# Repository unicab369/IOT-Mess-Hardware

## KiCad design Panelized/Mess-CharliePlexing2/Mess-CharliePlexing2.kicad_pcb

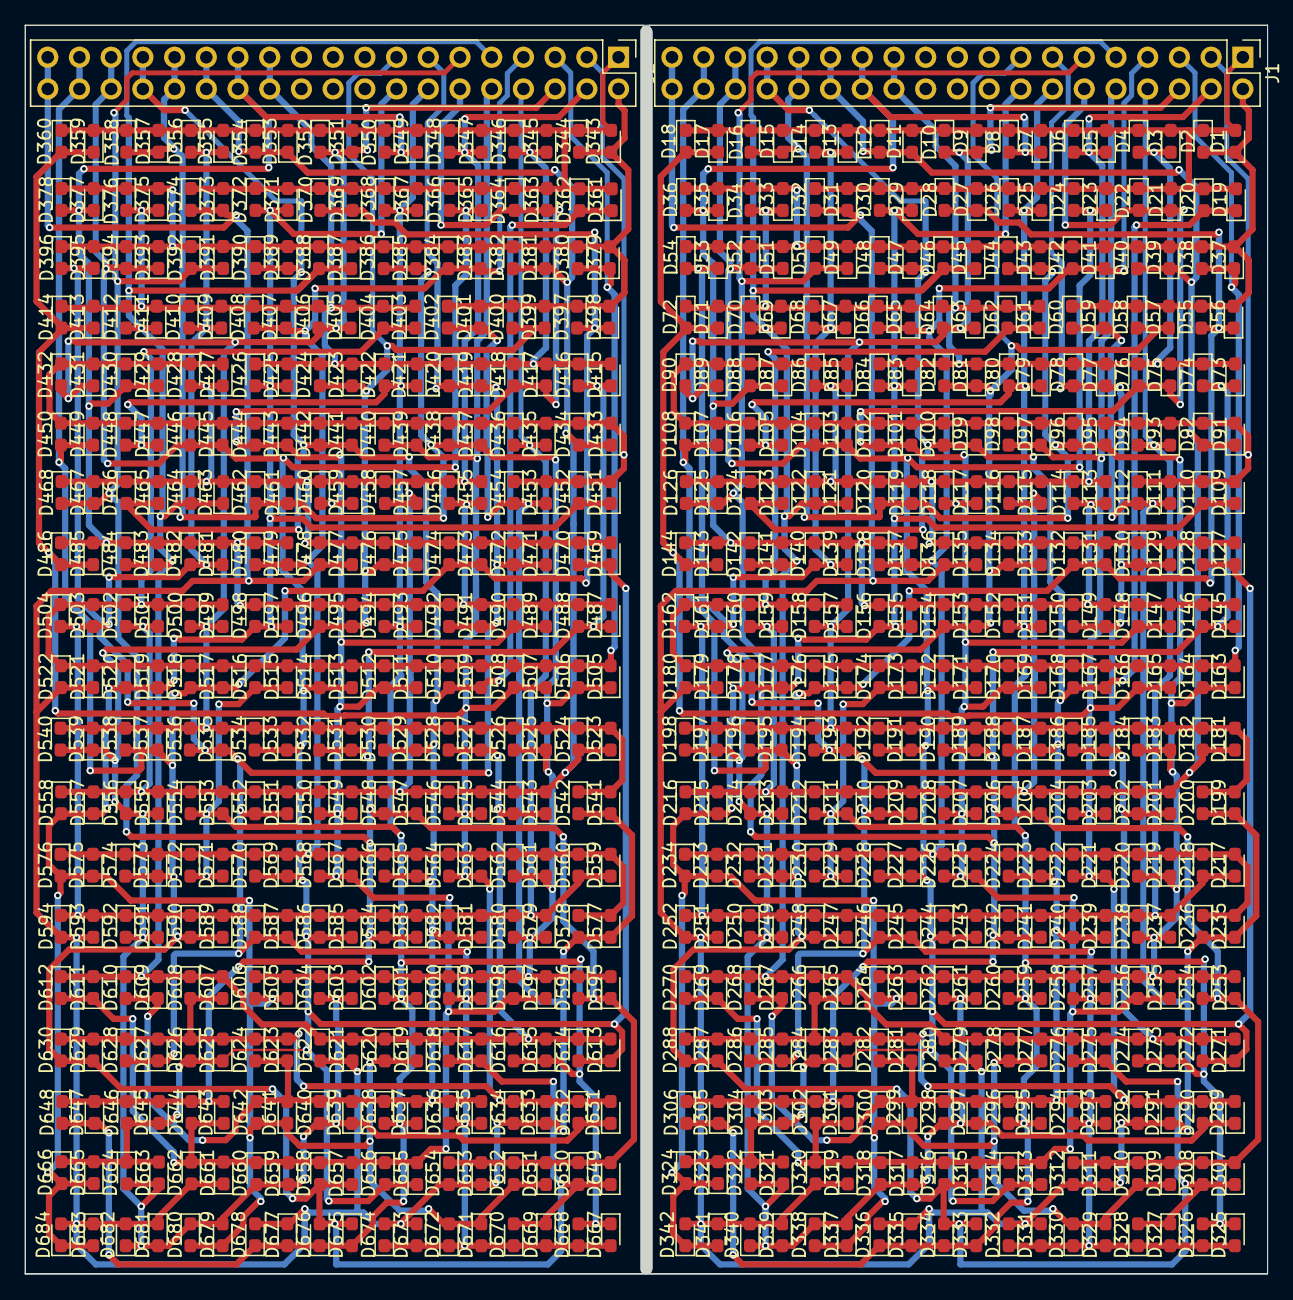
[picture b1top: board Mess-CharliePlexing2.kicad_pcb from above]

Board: 2 copper layers, 99.5 x 100.0 mm, 686 parts (0 on the bottom side), 24 nets.

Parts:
D1, D2, D3, D4, D5, D6, D7, D8, D9, D10, D11, D12, D13, D14, D15, D16, D17, D18, D19, D20, D21, D22, D23, D24, D25, D26, D27, D28, D29, D30, D31, D32, D33, D34, D35, D36, D37, D38, D39, D40, D41, D42, D43, D44, D45, D46, D47, D48, D49, D50, D51, D52, D53, D54, D55, D56, D57, D58, D59, D60, D61, D62, D63, D64, D65, D66, D67, D68, D69, D70, D71, D72, D73, D74, D75, D76, D77, D78, D79, D80, D81, D82, D83, D84, D85, D86, D87, D88, D89, D90, D91, D92, D93, D94, D95, D96, D97, D98, D99, D100, D101, D102, D103, D104, D105, D106, D107, D108, D109, D110, D111, D112, D113, D114, D115, D116, D117, D118, D119, D120, D121, D122, D123, D124, D125, D126, D127, D128, D129, D130, D131, D132, D133, D134, D135, D136, D137, D138, D139, D140, D141, D142, D143, D144, D145, D146, D147, D148, D149, D150, D151, D152, D153, D154, D155, D156, D157, D158, D159, D160, D161, D162, D163, D164, D165, D166, D167, D168, D169, D170, D171, D172, D173, D174, D175, D176, D177, D178, D179, D180, D181, D182, D183, D184, D185, D186, D187, D188, D189, D190, D191, D192, D193, D194, D195, D196, D197, D198, D199, D200, D201, D202, D203, D204, D205, D206, D207, D208, D209, D210, D211, D212, D213, D214, D215, D216, D217, D218, D219, D220, D221, D222, D223, D224, D225, D226, D227, D228, D229, D230, D231, D232, D233, D234, D235, D236, D237, D238, D239, D240, D241, D242, D243, D244, D245, D246, D247, D248, D249, D250, D251, D252, D253, D254, D255, D256, D257, D258, D259, D260, D261, D262, D263, D264, D265, D266, D267, D268, D269, D270, D271, D272, D273, D274, D275, D276, D277, D278, D279, D280, D281, D282, D283, D284, D285, D286, D287, D288, D289, D290, D291, D292, D293, D294, D295, D296, D297, D298, D299, D300, D301, D302, D303, D304, D305, D306, D307, D308, D309, D310, D311, D312, D313, D314, D315, D316, D317, D318, D319, D320, D321, D322, D323, D324, D325, D326, D327, D328, D329, D330, D331, D332, D333, D334, D335, D336, D337, D338, D339, D340, D341, D342, D343, D344, D345, D346, D347, D348, D349, D350, D351, D352, D353, D354, D355, D356, D357, D358, D359, D360, D361, D362, D363, D364, D365, D366, D367, D368, D369, D370, D371, D372, D373, D374, D375, D376, D377, D378, D379, D380, D381, D382, D383, D384, D385, D386, D387, D388, D389, D390, D391, D392, D393, D394, D395, D396, D397, D398, D399, D400, D401, D402, D403, D404, D405, D406, D407, D408, D409, D410, D411, D412, D413, D414, D415, D416, D417, D418, D419, D420, D421, D422, D423, D424, D425, D426, D427, D428, D429, D430, D431, D432, D433, D434, D435, D436, D437, D438, D439, D440, D441, D442, D443, D444, D445, D446, D447, D448, D449, D450, D451, D452, D453, D454, D455, D456, D457, D458, D459, D460, D461, D462, D463, D464, D465, D466, D467, D468, D469, D470, D471, D472, D473, D474, D475, D476, D477, D478, D479, D480, D481, D482, D483, D484, D485, D486, D487, D488, D489, D490, D491, D492, D493, D494, D495, D496, D497, D498, D499, D500, D501, D502, D503, D504, D505, D506, D507, D508, D509, D510, D511, D512, D513, D514, D515, D516, D517, D518, D519, D520, D521, D522, D523, D524, D525, D526, D527, D528, D529, D530, D531, D532, D533, D534, D535, D536, D537, D538, D539, D540, D541, D542, D543, D544, D545, D546, D547, D548, D549, D550, D551, D552, D553, D554, D555, D556, D557, D558, D559, D560, D561, D562, D563, D564, D565, D566, D567, D568, D569, D570, D571, D572, D573, D574, D575, D576, D577, D578, D579, D580, D581, D582, D583, D584, D585, D586, D587, D588, D589, D590, D591, D592, D593, D594, D595, D596, D597, D598, D599, D600, D601, D602, D603, D604, D605, D606, D607, D608, D609, D610, D611, D612, D613, D614, D615, D616, D617, D618, D619, D620, D621, D622, D623, D624, D625, D626, D627, D628, D629, D630, D631, D632, D633, D634, D635, D636, D637, D638, D639, D640, D641, D642, D643, D644, D645, D646, D647, D648, D649, D650, D651, D652, D653, D654, D655, D656, D657, D658, D659, D660, D661, D662, D663, D664, D665, D666, D667, D668, D669, D670, D671, D672, D673, D674, D675, D676, D677, D678, D679, D680, D681, D682, D683, D684: LED; LED_0603_1608Metric_Pad1.05x0.95mm_HandSolder
J1, J2: Conn_02x19_Odd_Even; PinHeader_2x19_P2.54mm_Vertical

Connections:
A_0: D1.2 (A), D2.1 (K), D3.2 (A), D4.1 (K), D5.2 (A), D6.1 (K), D7.2 (A), D8.1 (K), D9.2 (A), D10.1 (K), D11.2 (A), D12.1 (K), D13.2 (A), D14.1 (K), D15.2 (A), D16.1 (K), D17.2 (A), D18.1 (K), D19.2 (A), D20.1 (K), D21.2 (A), D22.1 (K), D23.2 (A), D24.1 (K), D25.2 (A), D26.1 (K), D27.2 (A), D28.1 (K), D29.2 (A), D30.1 (K), D31.2 (A), D32.1 (K), D343.2 (A), D344.1 (K), D345.2 (A), D346.1 (K), D347.2 (A), D348.1 (K), D349.2 (A), D350.1 (K), D351.2 (A), D352.1 (K), D353.2 (A), D354.1 (K), D355.2 (A), D356.1 (K), D357.2 (A), D358.1 (K), D359.2 (A), D360.1 (K), D361.2 (A), D362.1 (K), D363.2 (A), D364.1 (K), D365.2 (A), D366.1 (K), D367.2 (A), D368.1 (K), D369.2 (A), D370.1 (K), D371.2 (A), D372.1 (K), D373.2 (A), D374.1 (K), J1.1, J2.1
A_1: D85.2 (A), D86.1 (K), D87.2 (A), D88.1 (K), D89.2 (A), D90.1 (K), D91.2 (A), D92.1 (K), D93.2 (A), D94.1 (K), D95.2 (A), D96.1 (K), D97.2 (A), D98.1 (K), D99.2 (A), D100.1 (K), D101.2 (A), D102.1 (K), D103.2 (A), D104.1 (K), D105.2 (A), D106.1 (K), D107.2 (A), D108.1 (K), D109.2 (A), D110.1 (K), D111.2 (A), D112.1 (K), D427.2 (A), D428.1 (K), D429.2 (A), D430.1 (K), D431.2 (A), D432.1 (K), D433.2 (A), D434.1 (K), D435.2 (A), D436.1 (K), D437.2 (A), D438.1 (K), D439.2 (A), D440.1 (K), D441.2 (A), D442.1 (K), D443.2 (A), D444.1 (K), D445.2 (A), D446.1 (K), D447.2 (A), D448.1 (K), D449.2 (A), D450.1 (K), D451.2 (A), D452.1 (K), D453.2 (A), D454.1 (K), J1.3, J2.3
A_2: D37.1 (K), D38.2 (A), D61.1 (K), D62.2 (A), D157.2 (A), D158.1 (K), D159.2 (A), D160.1 (K), D161.2 (A), D162.1 (K), D163.2 (A), D164.1 (K), D165.2 (A), D166.1 (K), D167.2 (A), D168.1 (K), D169.2 (A), D170.1 (K), D171.2 (A), D172.1 (K), D173.2 (A), D174.1 (K), D175.2 (A), D176.1 (K), D177.2 (A), D178.1 (K), D179.2 (A), D180.1 (K), D379.1 (K), D380.2 (A), D403.1 (K), D404.2 (A), D499.2 (A), D500.1 (K), D501.2 (A), D502.1 (K), D503.2 (A), D504.1 (K), D505.2 (A), D506.1 (K), D507.2 (A), D508.1 (K), D509.2 (A), D510.1 (K), D511.2 (A), D512.1 (K), D513.2 (A), D514.1 (K), D515.2 (A), D516.1 (K), D517.2 (A), D518.1 (K), D519.2 (A), D520.1 (K), D521.2 (A), D522.1 (K), J1.5, J2.5
A_3: D41.1 (K), D42.2 (A), D65.1 (K), D66.2 (A), D117.1 (K), D118.2 (A), D137.1 (K), D138.2 (A), D217.2 (A), D218.1 (K), D219.2 (A), D220.1 (K), D221.2 (A), D222.1 (K), D223.2 (A), D224.1 (K), D225.2 (A), D226.1 (K), D227.2 (A), D228.1 (K), D229.2 (A), D230.1 (K), D231.2 (A), D232.1 (K), D233.2 (A), D234.1 (K), D235.2 (A), D236.1 (K), D383.1 (K), D384.2 (A), D407.1 (K), D408.2 (A), D459.1 (K), D460.2 (A), D479.1 (K), D480.2 (A), D559.2 (A), D560.1 (K), D561.2 (A), D562.1 (K), D563.2 (A), D564.1 (K), D565.2 (A), D566.1 (K), D567.2 (A), D568.1 (K), D569.2 (A), D570.1 (K), D571.2 (A), D572.1 (K), D573.2 (A), D574.1 (K), D575.2 (A), D576.1 (K), D577.2 (A), D578.1 (K), J1.7, J2.7
A_4: D45.1 (K), D46.2 (A), D69.1 (K), D70.2 (A), D121.1 (K), D122.2 (A), D141.1 (K), D142.2 (A), D185.1 (K), D186.2 (A), D201.1 (K), D202.2 (A), D265.2 (A), D266.1 (K), D267.2 (A), D268.1 (K), D269.2 (A), D270.1 (K), D271.2 (A), D272.1 (K), D273.2 (A), D274.1 (K), D275.2 (A), D276.1 (K), D277.2 (A), D278.1 (K), D279.2 (A), D280.1 (K), D387.1 (K), D388.2 (A), D411.1 (K), D412.2 (A), D463.1 (K), D464.2 (A), D483.1 (K), D484.2 (A), D527.1 (K), D528.2 (A), D543.1 (K), D544.2 (A), D607.2 (A), D608.1 (K), D609.2 (A), D610.1 (K), D611.2 (A), D612.1 (K), D613.2 (A), D614.1 (K), D615.2 (A), D616.1 (K), D617.2 (A), D618.1 (K), D619.2 (A), D620.1 (K), D621.2 (A), D622.1 (K), J1.9, J2.9
A_5: D49.1 (K), D50.2 (A), D73.1 (K), D74.2 (A), D125.1 (K), D126.2 (A), D145.1 (K), D146.2 (A), D189.1 (K), D190.2 (A), D205.1 (K), D206.2 (A), D241.1 (K), D242.2 (A), D253.1 (K), D254.2 (A), D301.2 (A), D302.1 (K), D303.2 (A), D304.1 (K), D305.2 (A), D306.1 (K), D307.2 (A), D308.1 (K), D309.2 (A), D310.1 (K), D311.2 (A), D312.1 (K), D391.1 (K), D392.2 (A), D415.1 (K), D416.2 (A), D467.1 (K), D468.2 (A), D487.1 (K), D488.2 (A), D531.1 (K), D532.2 (A), D547.1 (K), D548.2 (A), D583.1 (K), D584.2 (A), D595.1 (K), D596.2 (A), D643.2 (A), D644.1 (K), D645.2 (A), D646.1 (K), D647.2 (A), D648.1 (K), D649.2 (A), D650.1 (K), D651.2 (A), D652.1 (K), D653.2 (A), D654.1 (K), J1.11, J2.11
A_6: D53.1 (K), D54.2 (A), D77.1 (K), D78.2 (A), D129.1 (K), D130.2 (A), D149.1 (K), D150.2 (A), D193.1 (K), D194.2 (A), D209.1 (K), D210.2 (A), D245.1 (K), D246.2 (A), D257.1 (K), D258.2 (A), D285.1 (K), D286.2 (A), D293.1 (K), D294.2 (A), D325.2 (A), D326.1 (K), D327.2 (A), D328.1 (K), D329.2 (A), D330.1 (K), D331.2 (A), D332.1 (K), D395.1 (K), D396.2 (A), D419.1 (K), D420.2 (A), D471.1 (K), D472.2 (A), D491.1 (K), D492.2 (A), D535.1 (K), D536.2 (A), D551.1 (K), D552.2 (A), D587.1 (K), D588.2 (A), D599.1 (K), D600.2 (A), D627.1 (K), D628.2 (A), D635.1 (K), D636.2 (A), D667.2 (A), D668.1 (K), D669.2 (A), D670.1 (K), D671.2 (A), D672.1 (K), D673.2 (A), D674.1 (K), J1.13, J2.13
A_7: D57.1 (K), D58.2 (A), D81.1 (K), D82.2 (A), D133.1 (K), D134.2 (A), D153.1 (K), D154.2 (A), D197.1 (K), D198.2 (A), D213.1 (K), D214.2 (A), D249.1 (K), D250.2 (A), D261.1 (K), D262.2 (A), D289.1 (K), D290.2 (A), D297.1 (K), D298.2 (A), D317.1 (K), D318.2 (A), D321.1 (K), D322.2 (A), D337.2 (A), D338.1 (K), D339.2 (A), D340.1 (K), D399.1 (K), D400.2 (A), D423.1 (K), D424.2 (A), D475.1 (K), D476.2 (A), D495.1 (K), D496.2 (A), D539.1 (K), D540.2 (A), D555.1 (K), D556.2 (A), D591.1 (K), D592.2 (A), D603.1 (K), D604.2 (A), D631.1 (K), D632.2 (A), D639.1 (K), D640.2 (A), D659.1 (K), D660.2 (A), D663.1 (K), D664.2 (A), D679.2 (A), D680.1 (K), D681.2 (A), D682.1 (K), J1.15, J2.15
C_0: D3.1 (K), D4.2 (A), D33.1 (K), D34.2 (A), D61.2 (A), D62.1 (K), D63.2 (A), D64.1 (K), D65.2 (A), D66.1 (K), D67.2 (A), D68.1 (K), D69.2 (A), D70.1 (K), D71.2 (A), D72.1 (K), D73.2 (A), D74.1 (K), D75.2 (A), D76.1 (K), D77.2 (A), D78.1 (K), D79.2 (A), D80.1 (K), D81.2 (A), D82.1 (K), D83.2 (A), D84.1 (K), D345.1 (K), D346.2 (A), D375.1 (K), D376.2 (A), D403.2 (A), D404.1 (K), D405.2 (A), D406.1 (K), D407.2 (A), D408.1 (K), D409.2 (A), D410.1 (K), D411.2 (A), D412.1 (K), D413.2 (A), D414.1 (K), D415.2 (A), D416.1 (K), D417.2 (A), D418.1 (K), D419.2 (A), D420.1 (K), D421.2 (A), D422.1 (K), D423.2 (A), D424.1 (K), D425.2 (A), D426.1 (K), J1.23, J1.24, J2.23, J2.24
C_1: D7.1 (K), D8.2 (A), D35.1 (K), D36.2 (A), D87.1 (K), D88.2 (A), D113.1 (K), D114.2 (A), D137.2 (A), D138.1 (K), D139.2 (A), D140.1 (K), D141.2 (A), D142.1 (K), D143.2 (A), D144.1 (K), D145.2 (A), D146.1 (K), D147.2 (A), D148.1 (K), D149.2 (A), D150.1 (K), D151.2 (A), D152.1 (K), D153.2 (A), D154.1 (K), D155.2 (A), D156.1 (K), D349.1 (K), D350.2 (A), D377.1 (K), D378.2 (A), D429.1 (K), D430.2 (A), D455.1 (K), D456.2 (A), D479.2 (A), D480.1 (K), D481.2 (A), D482.1 (K), D483.2 (A), D484.1 (K), D485.2 (A), D486.1 (K), D487.2 (A), D488.1 (K), D489.2 (A), D490.1 (K), D491.2 (A), D492.1 (K), D493.2 (A), D494.1 (K), D495.2 (A), D496.1 (K), D497.2 (A), D498.1 (K), J1.25, J1.26, J2.25, J2.26
C_2: D11.1 (K), D12.2 (A), D39.1 (K), D40.2 (A), D91.1 (K), D92.2 (A), D115.1 (K), D116.2 (A), D159.1 (K), D160.2 (A), D181.1 (K), D182.2 (A), D201.2 (A), D202.1 (K), D203.2 (A), D204.1 (K), D205.2 (A), D206.1 (K), D207.2 (A), D208.1 (K), D209.2 (A), D210.1 (K), D211.2 (A), D212.1 (K), D213.2 (A), D214.1 (K), D215.2 (A), D216.1 (K), D353.1 (K), D354.2 (A), D381.1 (K), D382.2 (A), D433.1 (K), D434.2 (A), D457.1 (K), D458.2 (A), D501.1 (K), D502.2 (A), D523.1 (K), D524.2 (A), D543.2 (A), D544.1 (K), D545.2 (A), D546.1 (K), D547.2 (A), D548.1 (K), D549.2 (A), D550.1 (K), D551.2 (A), D552.1 (K), D553.2 (A), D554.1 (K), D555.2 (A), D556.1 (K), D557.2 (A), D558.1 (K), J1.27, J1.28, J2.27, J2.28
C_3: D15.1 (K), D16.2 (A), D43.1 (K), D44.2 (A), D95.1 (K), D96.2 (A), D119.1 (K), D120.2 (A), D163.1 (K), D164.2 (A), D183.1 (K), D184.2 (A), D219.1 (K), D220.2 (A), D237.1 (K), D238.2 (A), D253.2 (A), D254.1 (K), D255.2 (A), D256.1 (K), D257.2 (A), D258.1 (K), D259.2 (A), D260.1 (K), D261.2 (A), D262.1 (K), D263.2 (A), D264.1 (K), D357.1 (K), D358.2 (A), D385.1 (K), D386.2 (A), D437.1 (K), D438.2 (A), D461.1 (K), D462.2 (A), D505.1 (K), D506.2 (A), D525.1 (K), D526.2 (A), D561.1 (K), D562.2 (A), D579.1 (K), D580.2 (A), D595.2 (A), D596.1 (K), D597.2 (A), D598.1 (K), D599.2 (A), D600.1 (K), D601.2 (A), D602.1 (K), D603.2 (A), D604.1 (K), D605.2 (A), D606.1 (K), J1.29, J1.30, J2.29, J2.30
C_4: D19.1 (K), D20.2 (A), D47.1 (K), D48.2 (A), D99.1 (K), D100.2 (A), D123.1 (K), D124.2 (A), D167.1 (K), D168.2 (A), D187.1 (K), D188.2 (A), D223.1 (K), D224.2 (A), D239.1 (K), D240.2 (A), D267.1 (K), D268.2 (A), D281.1 (K), D282.2 (A), D293.2 (A), D294.1 (K), D295.2 (A), D296.1 (K), D297.2 (A), D298.1 (K), D299.2 (A), D300.1 (K), D361.1 (K), D362.2 (A), D389.1 (K), D390.2 (A), D441.1 (K), D442.2 (A), D465.1 (K), D466.2 (A), D509.1 (K), D510.2 (A), D529.1 (K), D530.2 (A), D565.1 (K), D566.2 (A), D581.1 (K), D582.2 (A), D609.1 (K), D610.2 (A), D623.1 (K), D624.2 (A), D635.2 (A), D636.1 (K), D637.2 (A), D638.1 (K), D639.2 (A), D640.1 (K), D641.2 (A), D642.1 (K), J1.31, J1.32, J2.31, J2.32
C_5: D23.1 (K), D24.2 (A), D51.1 (K), D52.2 (A), D103.1 (K), D104.2 (A), D127.1 (K), D128.2 (A), D171.1 (K), D172.2 (A), D191.1 (K), D192.2 (A), D227.1 (K), D228.2 (A), D243.1 (K), D244.2 (A), D271.1 (K), D272.2 (A), D283.1 (K), D284.2 (A), D303.1 (K), D304.2 (A), D313.1 (K), D314.2 (A), D321.2 (A), D322.1 (K), D323.2 (A), D324.1 (K), D365.1 (K), D366.2 (A), D393.1 (K), D394.2 (A), D445.1 (K), D446.2 (A), D469.1 (K), D470.2 (A), D513.1 (K), D514.2 (A), D533.1 (K), D534.2 (A), D569.1 (K), D570.2 (A), D585.1 (K), D586.2 (A), D613.1 (K), D614.2 (A), D625.1 (K), D626.2 (A), D645.1 (K), D646.2 (A), D655.1 (K), D656.2 (A), D663.2 (A), D664.1 (K), D665.2 (A), D666.1 (K), J1.33, J1.34, J2.33, J2.34
C_6: D27.1 (K), D28.2 (A), D55.1 (K), D56.2 (A), D107.1 (K), D108.2 (A), D131.1 (K), D132.2 (A), D175.1 (K), D176.2 (A), D195.1 (K), D196.2 (A), D231.1 (K), D232.2 (A), D247.1 (K), D248.2 (A), D275.1 (K), D276.2 (A), D287.1 (K), D288.2 (A), D307.1 (K), D308.2 (A), D315.1 (K), D316.2 (A), D327.1 (K), D328.2 (A), D333.1 (K), D334.2 (A), D369.1 (K), D370.2 (A), D397.1 (K), D398.2 (A), D449.1 (K), D450.2 (A), D473.1 (K), D474.2 (A), D517.1 (K), D518.2 (A), D537.1 (K), D538.2 (A), D573.1 (K), D574.2 (A), D589.1 (K), D590.2 (A), D617.1 (K), D618.2 (A), D629.1 (K), D630.2 (A), D649.1 (K), D650.2 (A), D657.1 (K), D658.2 (A), D669.1 (K), D670.2 (A), D675.1 (K), D676.2 (A), J1.35, J1.36, J2.35, J2.36
C_7: D31.1 (K), D32.2 (A), D59.1 (K), D60.2 (A), D111.1 (K), D112.2 (A), D135.1 (K), D136.2 (A), D179.1 (K), D180.2 (A), D199.1 (K), D200.2 (A), D235.1 (K), D236.2 (A), D251.1 (K), D252.2 (A), D279.1 (K), D280.2 (A), D291.1 (K), D292.2 (A), D311.1 (K), D312.2 (A), D319.1 (K), D320.2 (A), D331.1 (K), D332.2 (A), D335.1 (K), D336.2 (A), D339.1 (K), D340.2 (A), D341.1 (K), D342.2 (A), D373.1 (K), D374.2 (A), D401.1 (K), D402.2 (A), D453.1 (K), D454.2 (A), D477.1 (K), D478.2 (A), D521.1 (K), D522.2 (A), D541.1 (K), D542.2 (A), D577.1 (K), D578.2 (A), D593.1 (K), D594.2 (A), D621.1 (K), D622.2 (A), D633.1 (K), D634.2 (A), D653.1 (K), D654.2 (A), D661.1 (K), D662.2 (A), D673.1 (K), D674.2 (A), D677.1 (K), D678.2 (A), D681.1 (K), D682.2 (A), D683.1 (K), D684.2 (A), J1.37, J1.38, J2.37, J2.38
R_0: D1.1 (K), D2.2 (A), D33.2 (A), D34.1 (K), D35.2 (A), D36.1 (K), D37.2 (A), D38.1 (K), D39.2 (A), D40.1 (K), D41.2 (A), D42.1 (K), D43.2 (A), D44.1 (K), D45.2 (A), D46.1 (K), D47.2 (A), D48.1 (K), D49.2 (A), D50.1 (K), D51.2 (A), D52.1 (K), D53.2 (A), D54.1 (K), D55.2 (A), D56.1 (K), D57.2 (A), D58.1 (K), D59.2 (A), D60.1 (K), D343.1 (K), D344.2 (A), D375.2 (A), D376.1 (K), D377.2 (A), D378.1 (K), D379.2 (A), D380.1 (K), D381.2 (A), D382.1 (K), D383.2 (A), D384.1 (K), D385.2 (A), D386.1 (K), D387.2 (A), D388.1 (K), D389.2 (A), D390.1 (K), D391.2 (A), D392.1 (K), D393.2 (A), D394.1 (K), D395.2 (A), D396.1 (K), D397.2 (A), D398.1 (K), D399.2 (A), D400.1 (K), D401.2 (A), D402.1 (K), J1.2, J2.2
R_1: D5.1 (K), D6.2 (A), D85.1 (K), D86.2 (A), D113.2 (A), D114.1 (K), D115.2 (A), D116.1 (K), D117.2 (A), D118.1 (K), D119.2 (A), D120.1 (K), D121.2 (A), D122.1 (K), D123.2 (A), D124.1 (K), D125.2 (A), D126.1 (K), D127.2 (A), D128.1 (K), D129.2 (A), D130.1 (K), D131.2 (A), D132.1 (K), D133.2 (A), D134.1 (K), D135.2 (A), D136.1 (K), D347.1 (K), D348.2 (A), D427.1 (K), D428.2 (A), D455.2 (A), D456.1 (K), D457.2 (A), D458.1 (K), D459.2 (A), D460.1 (K), D461.2 (A), D462.1 (K), D463.2 (A), D464.1 (K), D465.2 (A), D466.1 (K), D467.2 (A), D468.1 (K), D469.2 (A), D470.1 (K), D471.2 (A), D472.1 (K), D473.2 (A), D474.1 (K), D475.2 (A), D476.1 (K), D477.2 (A), D478.1 (K), J1.4, J2.4
R_2: D9.1 (K), D10.2 (A), D63.1 (K), D64.2 (A), D89.1 (K), D90.2 (A), D157.1 (K), D158.2 (A), D181.2 (A), D182.1 (K), D183.2 (A), D184.1 (K), D185.2 (A), D186.1 (K), D187.2 (A), D188.1 (K), D189.2 (A), D190.1 (K), D191.2 (A), D192.1 (K), D193.2 (A), D194.1 (K), D195.2 (A), D196.1 (K), D197.2 (A), D198.1 (K), D199.2 (A), D200.1 (K), D351.1 (K), D352.2 (A), D405.1 (K), D406.2 (A), D431.1 (K), D432.2 (A), D499.1 (K), D500.2 (A), D523.2 (A), D524.1 (K), D525.2 (A), D526.1 (K), D527.2 (A), D528.1 (K), D529.2 (A), D530.1 (K), D531.2 (A), D532.1 (K), D533.2 (A), D534.1 (K), D535.2 (A), D536.1 (K), D537.2 (A), D538.1 (K), D539.2 (A), D540.1 (K), D541.2 (A), D542.1 (K), J1.6, J2.6
R_3: D13.1 (K), D14.2 (A), D67.1 (K), D68.2 (A), D93.1 (K), D94.2 (A), D139.1 (K), D140.2 (A), D161.1 (K), D162.2 (A), D217.1 (K), D218.2 (A), D237.2 (A), D238.1 (K), D239.2 (A), D240.1 (K), D241.2 (A), D242.1 (K), D243.2 (A), D244.1 (K), D245.2 (A), D246.1 (K), D247.2 (A), D248.1 (K), D249.2 (A), D250.1 (K), D251.2 (A), D252.1 (K), D355.1 (K), D356.2 (A), D409.1 (K), D410.2 (A), D435.1 (K), D436.2 (A), D481.1 (K), D482.2 (A), D503.1 (K), D504.2 (A), D559.1 (K), D560.2 (A), D579.2 (A), D580.1 (K), D581.2 (A), D582.1 (K), D583.2 (A), D584.1 (K), D585.2 (A), D586.1 (K), D587.2 (A), D588.1 (K), D589.2 (A), D590.1 (K), D591.2 (A), D592.1 (K), D593.2 (A), D594.1 (K), J1.8, J2.8
R_4: D17.1 (K), D18.2 (A), D71.1 (K), D72.2 (A), D97.1 (K), D98.2 (A), D143.1 (K), D144.2 (A), D165.1 (K), D166.2 (A), D203.1 (K), D204.2 (A), D221.1 (K), D222.2 (A), D265.1 (K), D266.2 (A), D281.2 (A), D282.1 (K), D283.2 (A), D284.1 (K), D285.2 (A), D286.1 (K), D287.2 (A), D288.1 (K), D289.2 (A), D290.1 (K), D291.2 (A), D292.1 (K), D359.1 (K), D360.2 (A), D413.1 (K), D414.2 (A), D439.1 (K), D440.2 (A), D485.1 (K), D486.2 (A), D507.1 (K), D508.2 (A), D545.1 (K), D546.2 (A), D563.1 (K), D564.2 (A), D607.1 (K), D608.2 (A), D623.2 (A), D624.1 (K), D625.2 (A), D626.1 (K), D627.2 (A), D628.1 (K), D629.2 (A), D630.1 (K), D631.2 (A), D632.1 (K), D633.2 (A), D634.1 (K), J1.10, J2.10
R_5: D21.1 (K), D22.2 (A), D75.1 (K), D76.2 (A), D101.1 (K), D102.2 (A), D147.1 (K), D148.2 (A), D169.1 (K), D170.2 (A), D207.1 (K), D208.2 (A), D225.1 (K), D226.2 (A), D255.1 (K), D256.2 (A), D269.1 (K), D270.2 (A), D301.1 (K), D302.2 (A), D313.2 (A), D314.1 (K), D315.2 (A), D316.1 (K), D317.2 (A), D318.1 (K), D319.2 (A), D320.1 (K), D363.1 (K), D364.2 (A), D417.1 (K), D418.2 (A), D443.1 (K), D444.2 (A), D489.1 (K), D490.2 (A), D511.1 (K), D512.2 (A), D549.1 (K), D550.2 (A), D567.1 (K), D568.2 (A), D597.1 (K), D598.2 (A), D611.1 (K), D612.2 (A), D643.1 (K), D644.2 (A), D655.2 (A), D656.1 (K), D657.2 (A), D658.1 (K), D659.2 (A), D660.1 (K), D661.2 (A), D662.1 (K), J1.12, J2.12
R_6: D25.1 (K), D26.2 (A), D79.1 (K), D80.2 (A), D105.1 (K), D106.2 (A), D151.1 (K), D152.2 (A), D173.1 (K), D174.2 (A), D211.1 (K), D212.2 (A), D229.1 (K), D230.2 (A), D259.1 (K), D260.2 (A), D273.1 (K), D274.2 (A), D295.1 (K), D296.2 (A), D305.1 (K), D306.2 (A), D325.1 (K), D326.2 (A), D333.2 (A), D334.1 (K), D335.2 (A), D336.1 (K), D367.1 (K), D368.2 (A), D421.1 (K), D422.2 (A), D447.1 (K), D448.2 (A), D493.1 (K), D494.2 (A), D515.1 (K), D516.2 (A), D553.1 (K), D554.2 (A), D571.1 (K), D572.2 (A), D601.1 (K), D602.2 (A), D615.1 (K), D616.2 (A), D637.1 (K), D638.2 (A), D647.1 (K), D648.2 (A), D667.1 (K), D668.2 (A), D675.2 (A), D676.1 (K), D677.2 (A), D678.1 (K), J1.14, J2.14
R_7: D29.1 (K), D30.2 (A), D83.1 (K), D84.2 (A), D109.1 (K), D110.2 (A), D155.1 (K), D156.2 (A), D177.1 (K), D178.2 (A), D215.1 (K), D216.2 (A), D233.1 (K), D234.2 (A), D263.1 (K), D264.2 (A), D277.1 (K), D278.2 (A), D299.1 (K), D300.2 (A), D309.1 (K), D310.2 (A), D323.1 (K), D324.2 (A), D329.1 (K), D330.2 (A), D337.1 (K), D338.2 (A), D341.2 (A), D342.1 (K), D371.1 (K), D372.2 (A), D425.1 (K), D426.2 (A), D451.1 (K), D452.2 (A), D497.1 (K), D498.2 (A), D519.1 (K), D520.2 (A), D557.1 (K), D558.2 (A), D575.1 (K), D576.2 (A), D605.1 (K), D606.2 (A), D619.1 (K), D620.2 (A), D641.1 (K), D642.2 (A), D651.1 (K), D652.2 (A), D665.1 (K), D666.2 (A), D671.1 (K), D672.2 (A), D679.1 (K), D680.2 (A), D683.2 (A), D684.1 (K), J1.16, J2.16
